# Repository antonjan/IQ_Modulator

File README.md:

# IQ_Modulator for Cubesat Transmitter.
<br>
IQ Modulator for 2M generating IQ stream via Audio PCM codec as modelation and using I2C to controle the RF local oselator for the RF mixer. The modulated RF signal is the Amplified to about +27dbm. (estimated 500mW)<br>
I2C Control for LO Local Osxelator with IQ moualtor RF amp and SAW and Ceremic output filters to antenna.<br>
<b><This is not complete yet still designing ></b>
<br>
3d View<br>
<br>
#Component list
<br>  
# OBC and SDR  
I am considering using Orange Pi rather than Raspberry as it has build in Audio in and out with a smaller footprint<br>
An another advantage of the Orange Pi is the additional USB ports witch I want to enable for the RTL dongle to be used as receiver.<br>
The software concept was tested using gnuradio for transponder with a hackrf for TX and a rtl sdr dongle for RX.<br>
I am still working on the telemetry witch works on its own but I need to combine it with Gnuraio transponder.<br>
I have to telemetry modes at the moment CW send Calsign and cubesat name and settings. APRS 1200 FSK sending the status of transponder<br>
# Power
Total power usage of board still needs to be calculated but my estimation with full power is 2w including Orange pi.<br>
Power usage in sleep mode possibly 500mw<br>
The PCB design was done in Kicad<br>
<br>
# Project Status.
This project is not compleet yet. (Almost done 12/06/2018)  
My plan is to have it working by 15 July 2018.
The board V3 has the wrong pin configuration for U2 trf3701
I am now working on V4 ans need to get it working by 9 August 2018 for the BACAR6 baloon project.
# Todo
1) Real time clock (done) I had to remove the Real time clock as there is not enuf space on the PCB<br>
2) I2C pull up resistors (done)<br>
3) Maybe different 70cm filter. (2m filter was changed to discrete components pi 5 stage 40db down. The 70cm filter was removed as there was now space on the PCB)<br>
4) CS for ic's<br>
5) Temprature and Tx power measurementA/D. (The A/D was added using MCP3421A0T-E/CH and will read the power output of the MMZ09332BT1 30db power amp that should give us about +27dbm. This A/D reading can then be used to adjust the ALC level in the IQ stream)<br>
6) Battery and solar Voltage Monitoring (A/D) (I had to remove this as there was no space on the PCB Board)<br>
7) I forgot to add a 4k7 resistor to base of Q1. Fixed and is now added.
8) Board placement redone thats why I have vertion 3 as I could not root all routes.  
# Constranes 
1) Small Board to fit all components.
2) My Pick and Place machien can not place components smaller that 0805.  
# Software
The software for this Board will be in the following repository
https://github.com/antonjan/Balloon-Transponder

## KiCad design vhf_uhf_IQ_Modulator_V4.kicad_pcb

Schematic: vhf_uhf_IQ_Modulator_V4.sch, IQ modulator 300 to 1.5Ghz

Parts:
C1, C2, C3, C13, C15, C17, C20: 1uF 16V; CP_Tantalum_Case-R_EIA-2012-12_Reflow
C4: 3.3pF; C_0805_HandSoldering
C5, C8, C23, C25, C28: 10uF 16V; C_0805_HandSoldering
C6, C7, C11, C12: 2200pF; C_0805_HandSoldering
C9, C14: 1nF; C_0805_HandSoldering
C10: 4.7uF 16V; C_0805_HandSoldering
C16, C21: 100pF; C_0805_HandSoldering
C18: 27pF; C_0805_HandSoldering
C19, C26: 220pF; C_0805_HandSoldering
C22, C29, C30, C31: 33pF; C_0805_HandSoldering
C24: 15pF; C_0805_HandSoldering
C27: 100nF; C_0805_HandSoldering
J1: CONN_01X03; Pin_Header_Straight_1x03_Pitch2.54mm
J2: TEST_1P; Pin_Header_Straight_1x01_Pitch2.54mm
J3: Audio-Jack-3; Pin_Header_Straight_1x03_Pitch2.54mm
J4: CONN_01X04; Pin_Header_Straight_1x04_Pitch2.54mm
J5: SMA Edge FM; Molex_SMA_Jack_Edge_Mount
L1, L5: 33nF; C_0805_HandSoldering
L2, L4: 33nH; L_0805_HandSoldering
L3: 22nF; C_0805_HandSoldering
L6, L9: 56nH; L_0805_HandSoldering
L7, L8: 110nH; L_0805_HandSoldering
Q1, Q2, Q3: BC817-40; SOT-23
R1, R13: 10k; R_0805_HandSoldering
R2, R3, R5, R6: 1K; R_0805_HandSoldering
R4: 1k8; R_0805_HandSoldering
R7, R8, R14: 6k8; R_0805_HandSoldering
R9, R12: 0; R_0805_HandSoldering
R10: 2k2; R_0805_HandSoldering
R11: OC; R_0805_HandSoldering
R15, R16: 6k5; R_0805_HandSoldering
R17: 4k7; R_0805_HandSoldering
RV1, RV2: 4k7; Potentiometer_Bourns_3314G_Vertical
U1: TRF3701; VQFN-16_3x3mm
U2: MMZ09332BT1; QFN-12-1EP_3x3mm_P0.5mm_EP1.65x1.65mm
U3: Si570; Oscillator_SMD_SI570_SI571_HandSoldering
U4: Orange Pi zero; orangepi-zero
U5: MCP3421A0T-E/CH; SOT-23-6_Handsoldering

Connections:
+3V3: C17.1, J1.2, R7.2, U3.6, U4.101, U4.117
+5V: C1.1, C2.1, C3.1, C9.2, C10.1, C13.1, C14.2, C15.1, C16.2, C20.1, C27.2, C28.1, J1.1, J4.1, L1.1, L2.1, R1.2, R4.2, R10.2, R13.1, R15.1, R16.1, RV1.1, RV2.1, U1.6, U1.10, U2.2, U4.1, U4.102, U4.104, U5.5
GND: C1.2, C2.2, C3.2, C4.1, C6.2, C7.2, C9.1, C10.2, C11.2, C12.2, C13.2, C14.1, C15.2, C16.1, C17.2, C18.1, C20.2, C21.1, C22.1, C24.1, C27.1, C28.2, C29.1, C30.1, C31.1, J1.3, J3.3, J4.4, J5.2, L5.2, Q1.2 (E), Q2.2 (E), Q3.2 (E), R11.1, RV1.3, RV2.3, U1.1, U1.2, U1.3, U1.5, U1.9, U1.11, U1.12, U1.17, U3.3, U4.2, U4.106, U4.109, U4.114, U4.120, U4.125, U4.201, U5.2, U5.6
unnamed: C4.2, L1.2, U2.11
unnamed: C5.1, U4.8
unnamed: C5.2, R2.2
unnamed: C6.1, R2.1, R3.2
unnamed: C7.1, R3.1, U1.14
unnamed: C8.1, U4.7
unnamed: C8.2, R5.2
unnamed: C11.1, R5.1, R6.2
unnamed: C12.1, R6.1, U1.13
unnamed: C18.2, L3.1, U2.3
unnamed: C19.1, L4.1, L5.1
unnamed: C19.2, L2.2, U2.7, U2.8, U2.9
unnamed: C22.2, C26.2, L4.2
unnamed: C23.1, J3.2
unnamed: C23.2, U4.11
unnamed: C24.2, L3.2, U1.8
unnamed: C25.1, J3.1
unnamed: C25.2, U4.12
unnamed: C26.1, L6.2
unnamed: C29.2, L6.1, L7.2
unnamed: C30.2, L7.1, L8.2
unnamed: C31.2, L8.1, L9.2
unnamed: J2.1, U3.5
unnamed: J4.2, U4.116
unnamed: J4.3, U4.118
unnamed: J5.1, L9.1
unnamed: Q1.1 (B), R17.1
unnamed: Q1.3 (C), R1.1, U2.10
unnamed: Q2.1 (B), R8.2
unnamed: Q2.3 (C), R7.1, U3.2
unnamed: Q3.1 (B), R14.2
unnamed: Q3.3 (C), R13.2, U1.7
unnamed: R4.1, U2.12
unnamed: R9.1, U1.4
unnamed: R10.1, U2.1
unnamed: R9.2, R11.2, R12.1
unnamed: R12.2, U3.4
unnamed: RV1.2, U1.16
unnamed: RV2.2, U1.15
PA01: R17.2, U4.111
PA06: R8.1, U4.107
PA07: R14.1, U4.112
PDet: C21.2, U2.6, U5.1
SDA: R16.2, U3.7, U4.103, U5.4
SLC: R15.2, U3.8, U4.105, U5.3

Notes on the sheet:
Check Volatge
1200pF / fc= 132KHz 2200pF / fc=72KHz 3300pF / fc=48KHz 4700pF / fc=34KHz
27dBm 500 mW (max)

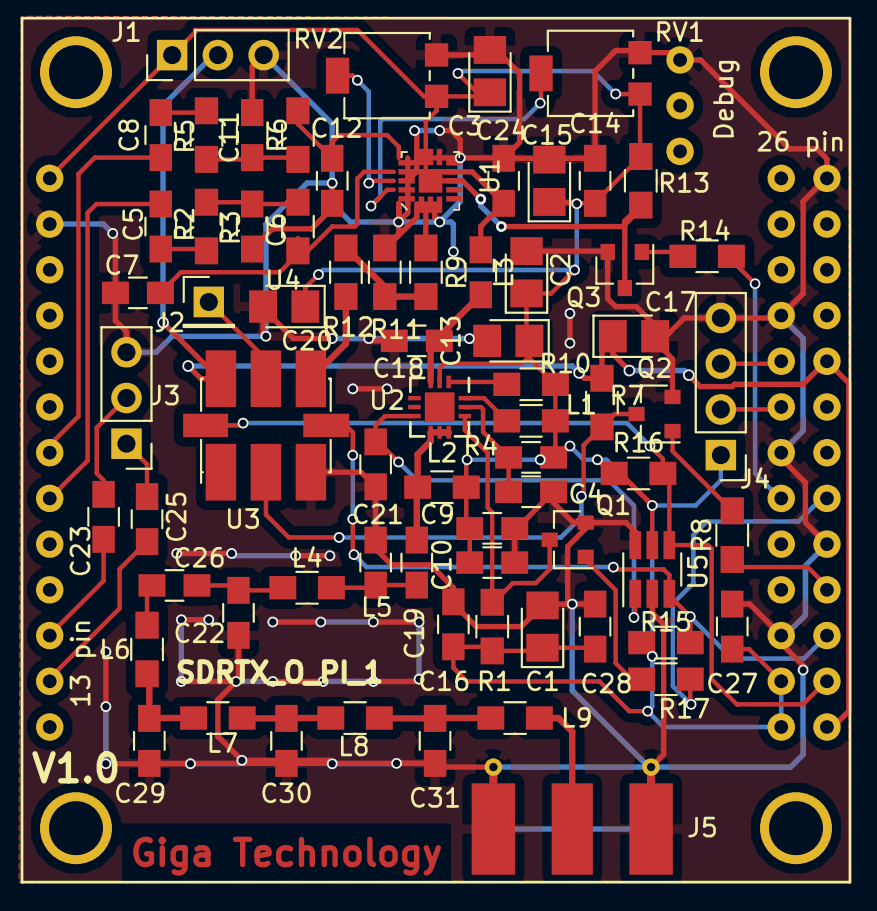
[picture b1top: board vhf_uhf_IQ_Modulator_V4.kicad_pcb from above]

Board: 2 copper layers, 72 parts (0 on the bottom side), 48 nets.

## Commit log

2017-11-21 Added some libraeries
2017-11-22 Adding docks and details in diagram
2017-11-27 moving docs to doc
2017-11-27 added rf switch
2017-11-27 added detail to readme
2017-11-27 added i and q ref voltage
2017-11-27 added power and usb
2017-11-30 added dokuments
2017-12-01 added PA IC dock
2017-12-02 added new PA 30dbm
2017-12-02 added dokumets
2017-12-02 added more setail
2017-12-03 adding PSK details
2018-02-12 Added real time clock
2018-02-12 Added more details on the to do list
2018-02-12 added mor information on the software and controler
2018-02-12 changed heading
2018-02-12 Fixed Spelling
2018-02-12 added a2d dock
2018-03-19 new simple diagram
2018-04-03 adding power amp details
2018-04-03 Adding RF Amp Dokuments ADL5601 and TQP&M9105
2018-06-01 2m filter and rf switch
2018-06-02 2m filter
2018-06-02 finilising Digarm
2018-06-03 Done Anotation
2018-06-03 Allocated Footprints
2018-06-03 Created Bom and pcbedge
2018-06-04 redused diagram to fit on pcb
2018-06-04 Trying to fic U3 Footprint
2018-06-05 Fixed all Footprints
2018-06-05 added Pots dock
2018-06-05 Added printable Diagram
2018-06-05 Added more Project Status details
2018-06-06 added Bom file
2018-06-06 Plased Components
2018-06-06 Adding PCB image
2018-06-06 fix image link
2018-06-06 Add Diagram
2018-06-06 Fix formatting
2018-06-06 add Component list
2018-06-06 Added Component list
2018-06-06 Placing components
2018-06-07 updated Parts list
2018-06-07 Placed all components
2018-06-07 add 3d view
2018-06-07 added 3d view
2018-06-07 PCB placement
2018-06-07 add pcb detail
2018-06-07 Plasing labels
2018-06-08 Adding diagram
2018-06-08 added Block Diagram
2018-06-08 Routing
2018-06-08 replace reademe
2018-06-09 More rooting
2018-06-10 23 tracks left
2018-06-10 19 tracks left
2018-06-11 add ver3 board
2018-06-11 Found library error
2018-06-11 fix lib and added Resistor
2018-06-12 added project compleeshion details
2018-06-12 added Constranes
2018-06-12 fix resistor
2018-06-12 Adding link to Software Repository
2018-06-12 fix formating
2018-07-05 ver3 Board plased
2018-07-05 Board now compleat with Groundplane
2018-07-06 added gerber files
2018-07-12 Adding Software Block Diagram
2018-08-01 beggining of V4 board
2018-08-01 V4 Board Compleat with Gerber
